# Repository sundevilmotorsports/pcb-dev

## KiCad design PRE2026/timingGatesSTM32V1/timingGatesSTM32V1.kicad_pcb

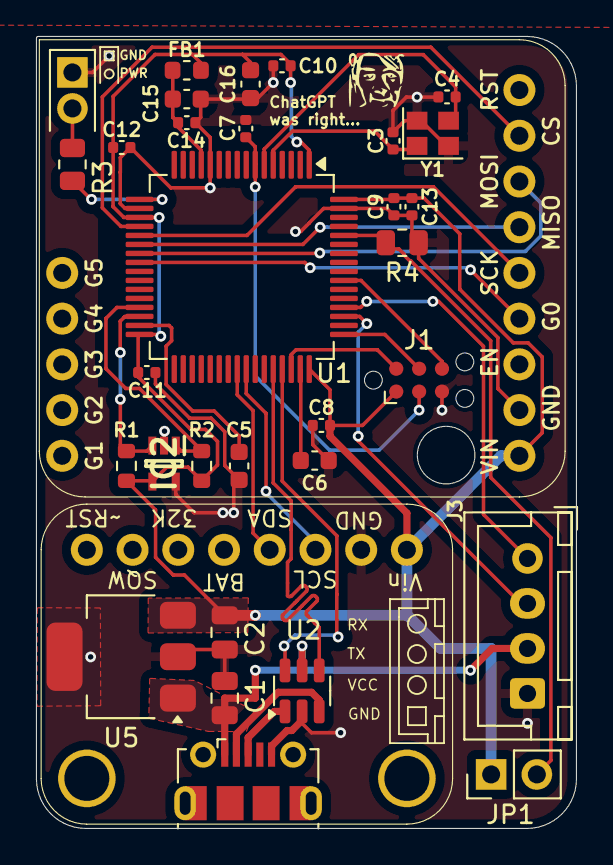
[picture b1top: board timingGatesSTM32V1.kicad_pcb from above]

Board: 4 copper layers, 30.0 x 44.0 mm, 34 parts (0 on the bottom side), 30 nets.

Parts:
C1, C2: 10uF; C_0805_2012Metric
C3, C4: 10pF; C_0402_1005Metric
C5, C6: 2.2uF; C_0603_1608Metric
C7, C8, C9, C10, C11, C12, C13, C14: 100nF; C_0402_1005Metric
C15, C16: 1uF; C_0603_1608Metric
D1: RED (floating); LED_0805_2012Metric
FB1: 120R; L_0603_1608Metric
H1: M3; MountingHole_3.2mm_M3
IC2: 24LC01BT-E_LT; SOT65P210X110-5N
J1: Conn_ARM_SWD_TagConnect_TC2030; Tag-Connect_TC2030-IDC-NL_2x03_P1.27mm_Vertical
J2: USB_B_Micro; USB_Micro-B_Molex-105017-0001
J3: Conn_01x04_Socket; JST_XH_B4B-XH-A_1x04_P2.50mm_Vertical
JP1: BOOT; PinHeader_1x02_P2.54mm_Vertical
R1, R2: 2.7k; R_0603_1608Metric
R3: 220; R_0805_2012Metric
R4: 10k; R_0805_2012Metric
U1: STM32F405RGT6; LQFP-64_10x10mm_P0.5mm
U2: USBLC6-2SC6; SOT-23-6
U3: RFM95W
U4: DS3231
U5: MIC37100-3.3WS; SOT-223-3_TabPin2
Y1: 12MHz; Crystal_SMD_2520-4Pin_2.5x2.0mm

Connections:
+3.3V: C2.1, C8.2, C9.2, C10.2, C11.2, C12.2, C13.2, C16.2, FB1.2, IC2.4 (VCC), J1.1 (VCC), JP1.1 (A), R1.2, R2.2, U1.1 (VBAT), U1.19 (VDD), U1.32 (VDD), U1.48 (VDD), U1.64 (VDD), U3.1 (Vin), U4.1 (Vin), U5.3 (OUT)
/BOOT0: JP1.2 (B), R4.2, U1.60 (BOOT0)
/G0: U1.24 (PC4), U3.4 (G0)
/HSE_IN: C3.1, U1.5 (PH0), Y1.1
/HSE_OUT: C4.1, U1.6 (PH1), Y1.3
/I2C2_SCL: IC2.1 (SCL), R2.1, U1.29 (PB10)
/I2C2_SDA: IC2.3 (SDA), R1.1, U1.30 (PB11)
/I2C3_SCL: U1.41 (PA8), U4.3 (SCL)
/I2C3_SDA: U1.40 (PC9), U4.4 (SDA)
/NRST: C7.2, J1.3 (~RESET), U1.7 (NRST)
/SPI1_MISO: U1.22 (PA6), U3.6 (MISO)
/SPI1_MOSI: U1.23 (PA7), U3.7 (MOSI)
/SPI1_NSS: U1.20 (PA4), U3.8 (CS)
/SPI1_SCK: U1.21 (PA5), U3.5 (SCK)
/SWCLK: J1.4 (SWCLK), U1.49 (PA14)
/SWDIO: J1.2 (SWDIO), U1.46 (PA13)
/SWO: J1.6 (SWO), U1.55 (PB3)
/USART3_RX: J3.1, U1.52 (PC11)
/USART3_TX: J3.2, U1.51 (PC10)
/USB_D+: U1.45 (PA12), U2.6 (I/O1)
/USB_D-: U1.44 (PA11), U2.4 (I/O2)
/VCAP_1: C5.1, U1.31 (VCAP_1)
/VCAP_2: C6.2, U1.47 (VCAP_2)
GND: C1.2, C2.2, C3.2, C4.2, C5.2, C6.1, C7.1, C8.1, C9.1, C10.1, C11.1, C12.1, C13.1, C14.1, C15.1, C16.1, D1.1 (K), IC2.2 (Vss), IC2.5 (WP), J1.5 (GND), J2.5 (GND), J3.4, R4.1, U1.12 (VSSA), U1.18 (VSS), U1.63 (VSS), U2.2 (GND), U3.2 (GND), U4.2 (GND), U5.2 (GND), Y1.2, Y1.4
unnamed: D1.2 (A), R3.1
unnamed: J2.3 (D+), U2.1 (I/O1)
unnamed: J2.2 (D-), U2.3 (I/O2)
unnamed: R3.2, U1.17 (PA3)
unnamed: C14.2, C15.2, FB1.1, U1.13 (VDDA)
VCC: C1.1, J2.1 (VBUS), J3.3, U2.5 (VBUS), U5.1 (IN)

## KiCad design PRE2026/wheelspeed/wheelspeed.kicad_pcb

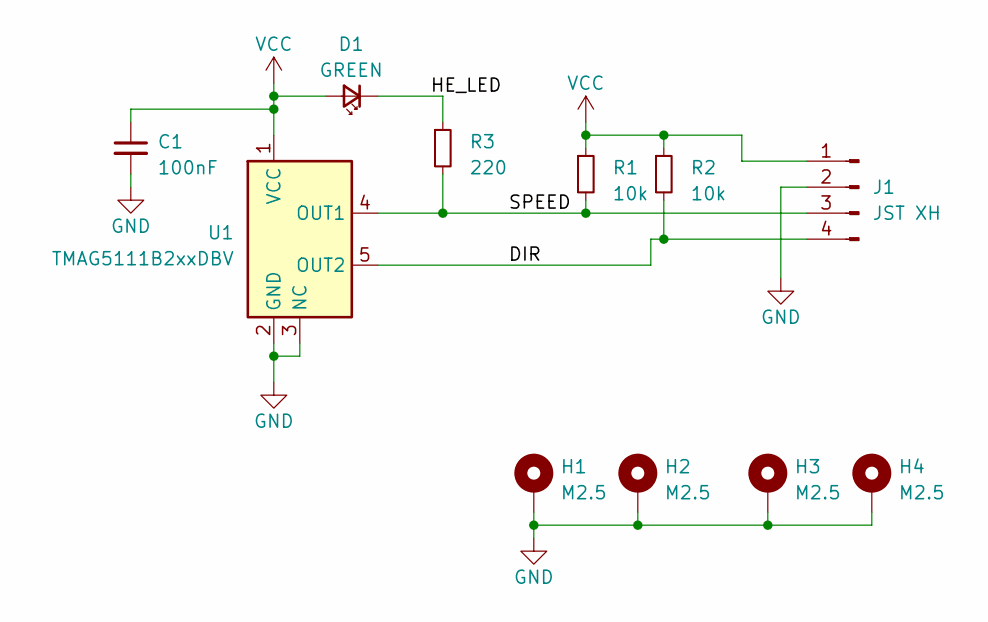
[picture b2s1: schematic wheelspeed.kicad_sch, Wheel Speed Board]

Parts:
C1: 100nF; C_0603_1608Metric
D1: GREEN; LED_1206_3216Metric
H1, H2, H3, H4: M2.5; MountingHole_2.7mm_M2.5_ISO7380_Pad
J1: JST XH; JST_XH_B4B-XH-AM_1x04_P2.50mm_Vertical
R1, R2: 10k; R_0805_2012Metric
R3: 220; R_0805_2012Metric
U1: TMAG5111B2xxDBV; SOT-23-5

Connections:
/DIR: J1.4, R2.2, U1.5 (OUT2)
/HE_LED: D1.1 (K), R3.1
/SPEED: J1.3, R1.2, R3.2, U1.4 (OUT1)
GND: C1.2, H1.1, H2.1, H3.1, H4.1, J1.2, U1.2 (GND), U1.3 (NC)
VCC: C1.1, D1.2 (A), J1.1, R1.1, R2.1, U1.1 (VCC)

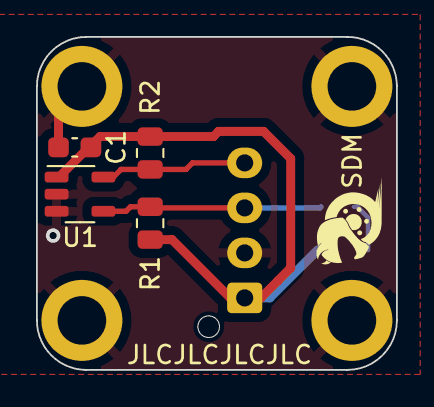
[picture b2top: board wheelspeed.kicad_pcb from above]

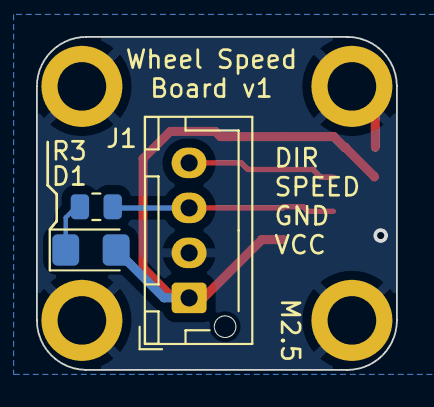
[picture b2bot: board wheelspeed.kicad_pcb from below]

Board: 2 copper layers, 20.0 x 18.5 mm, 11 parts (3 on the bottom side), 5 nets.

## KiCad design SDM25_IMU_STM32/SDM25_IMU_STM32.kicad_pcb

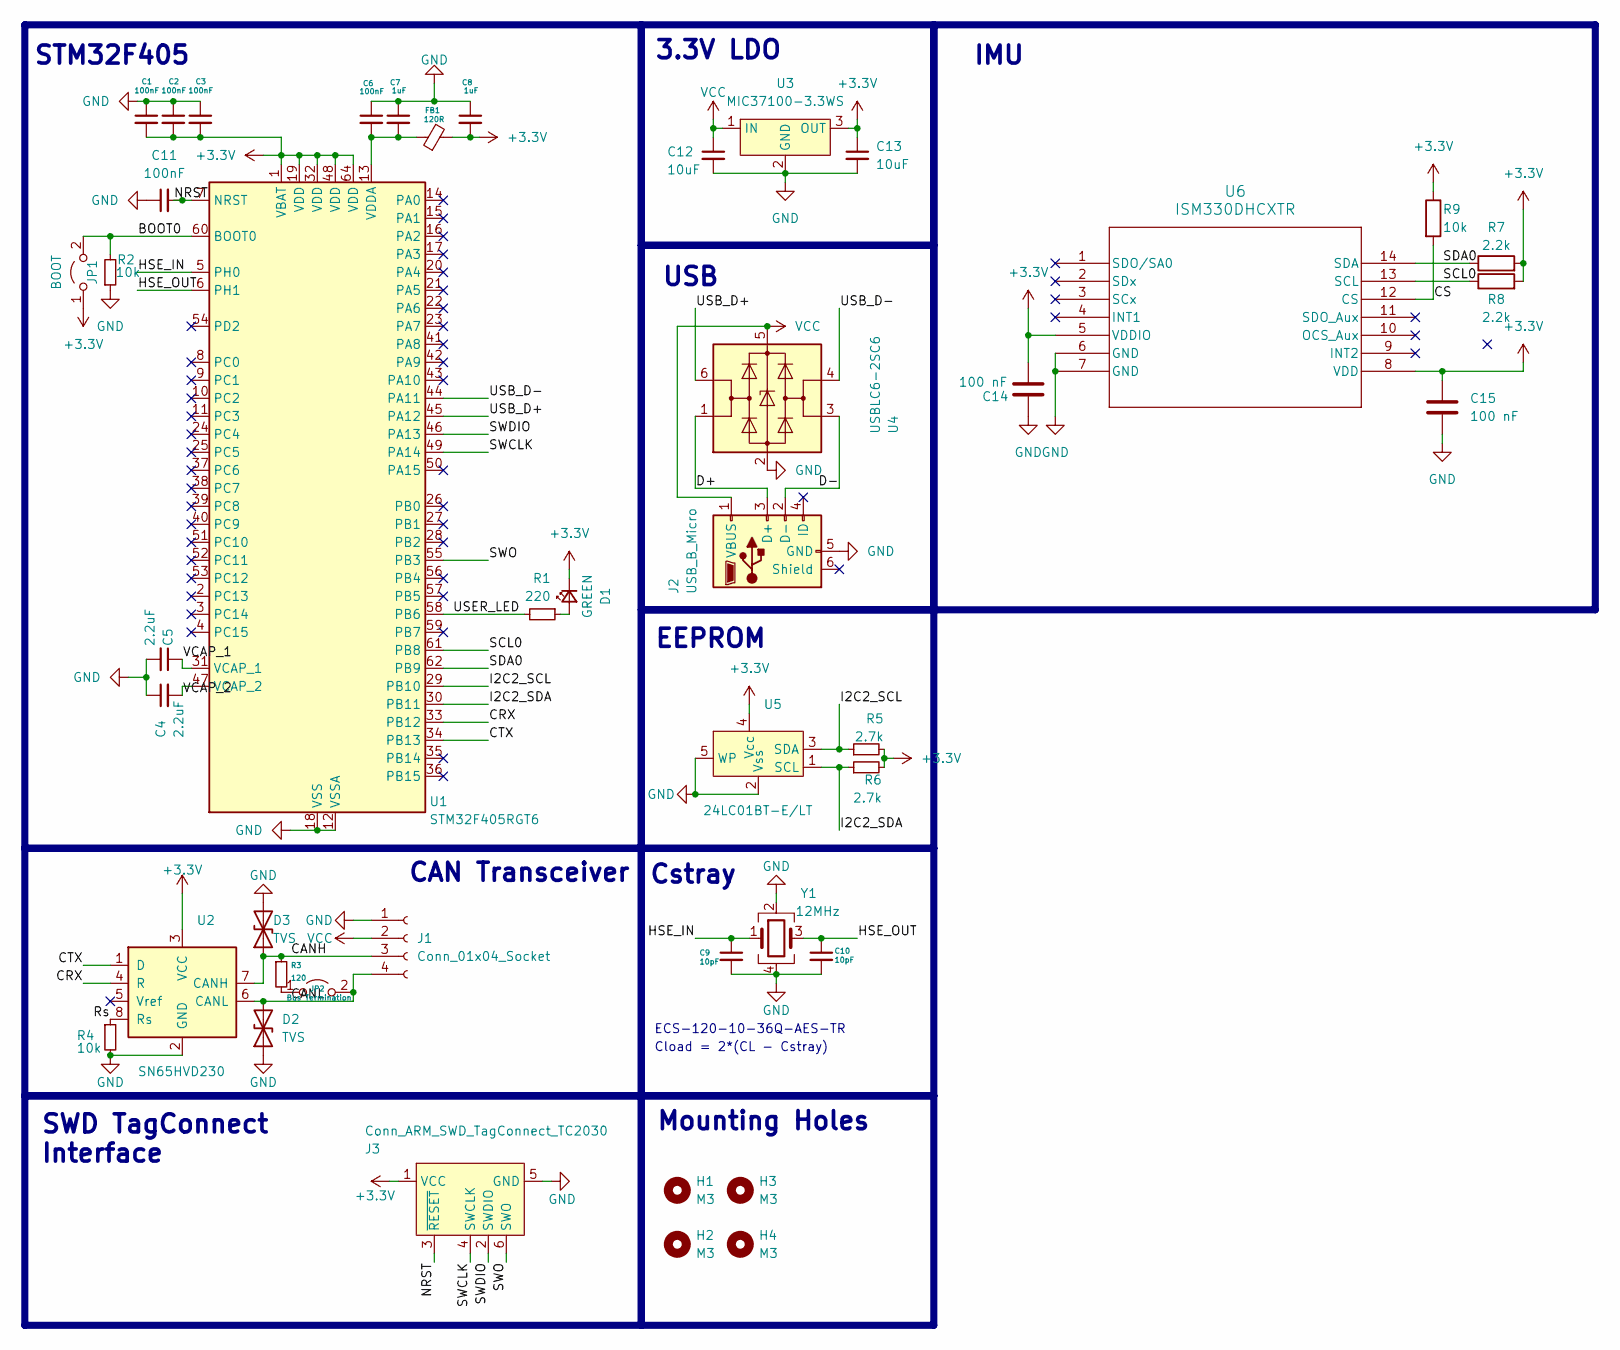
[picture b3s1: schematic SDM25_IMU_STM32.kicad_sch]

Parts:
C1, C2, C3, C6, C11: 100nF; C_0402_1005Metric
C4, C5: 2.2uF; C_0603_1608Metric
C7, C8: 1uF; C_0603_1608Metric
C9, C10: 10pF; C_0402_1005Metric
C12, C13: 10uF; C_0805_2012Metric
C14, C15: 100 nF; C_0402_1005Metric
D1: GREEN; LED_0805_2012Metric
D2, D3: TVS; SOD-123FL
FB1: 120R; L_0603_1608Metric
H1, H2, H3, H4: M3; MountingHole_3.2mm_M3
J1: Conn_01x04_Socket
J2: USB_B_Micro
J3: Conn_ARM_SWD_TagConnect_TC2030; Tag-Connect_TC2030-IDC-NL_2x03_P1.27mm_Vertical
JP1: BOOT; PinHeader_1x02_P2.54mm_Vertical
JP2: Bus Termination; PinHeader_1x02_P2.54mm_Vertical
R1: 220; R_0805_2012Metric
R2, R4, R9: 10k; R_0805_2012Metric
R3: 120; R_0603_1608Metric
R5, R6: 2.7k; R_0603_1608Metric
R7, R8: 2.2k; R_0603_1608Metric
U1: STM32F405RGT6; SOIC-8_3.9x4.9mm_P1.27mm
U2: SN65HVD230; LQFP-64_10x10mm_P0.5mm
U3: MIC37100-3.3WS; SC-70-5
U4: USBLC6-2SC6; SOT-23-6
U5: 24LC01BT-E/LT; SOT-223-3_TabPin2
U6: ISM330DHCXTR; LGA-14L
Y1: 12MHz; Crystal_SMD_2520-4Pin_2.5x2.0mm

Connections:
+3.3V: C1.2, C2.2, C3.2, C8.2, C13.1, C14.2, C15.1, D1.1 (K), FB1.2, J3.1 (VCC), JP1.1 (A), R5.2, R6.2, R7.2, R8.2, R9.1, U1.1 (VBAT), U1.19 (VDD), U1.32 (VDD), U1.48 (VDD), U1.64 (VDD), U2.3 (VCC), U3.3 (OUT), U5.4 (Vcc), U6.5 (VDDIO), U6.8 (VDD)
/BOOT0: JP1.2 (B), R2.2, U1.60 (BOOT0)
/CANH: D3.1 (A1), J1.3, R3.1, U2.7 (CANH)
/CANL: D2.2 (A2), J1.4, JP2.2 (B), U2.6 (CANL)
/CRX: U1.33 (PB13), U2.4 (R)
/CS: R9.2, U6.12 (CS)
/CTX: U1.34 (PB13), U2.1 (D)
/D+: J2.3 (D+), U4.1 (I/O1)
/D-: J2.2 (D-), U4.3 (I/O2)
/HSE_IN: C9.1, U1.5 (PH0), Y1.1
/HSE_OUT: C10.1, U1.6 (PH1), Y1.3
/I2C2_SCL: R5.1, U1.29 (PB10), U5.3 (SDA)
/I2C2_SDA: R6.1, U1.30 (PB11), U5.1 (SCL)
/NRST: C11.2, J3.3 (~RESET), U1.7 (NRST)
/Rs: R4.1, U2.8 (Rs)
/SCL0: R8.1, U1.61 (PB8), U6.13 (SCL)
/SDA0: R7.1, U1.62 (PB9), U6.14 (SDA)
/SWCLK: J3.4 (SWCLK), U1.49 (PA14)
/SWDIO: J3.2 (SWDIO), U1.46 (PA13)
/SWO: J3.6 (SWO), U1.55 (PB3)
/USB_D+: U1.45 (PA12), U4.6 (I/O1)
/USB_D-: U1.44 (PA11), U4.4 (I/O2)
/USER_LED: R1.2, U1.58 (PB6)
/VCAP_1: C5.1, U1.31 (VCAP_1)
/VCAP_2: C4.2, U1.47 (VCAP_2)
GND: C1.1, C2.1, C3.1, C4.1, C5.2, C6.1, C7.1, C8.1, C9.2, C10.2, C11.1, C12.2, C13.2, C14.1, C15.2, D2.1 (A1), D3.2 (A2), J1.1, J2.5 (GND), J3.5 (GND), R2.1, R4.2, U1.12 (VSSA), U1.18 (VSS), U1.63 (VSS), U2.2 (GND), U3.2 (GND), U4.2 (GND), U5.2 (Vss), U5.5 (WP), U6.6 (GND), U6.7 (GND), Y1.2, Y1.4
unnamed: D1.2 (A), R1.1
unnamed: JP2.1 (A), R3.2
unnamed: C6.2, C7.2, FB1.1, U1.13 (VDDA)
VCC: C12.1, J1.2, J2.1 (VBUS), U3.1 (IN), U4.5 (VBUS)

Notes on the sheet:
EEPROM
STM32F405
Cload = 2*(CL - Cstray)
IMU
Cstray
SWD TagConnect Interface
CAN Transceiver
ECS-120-10-36Q-AES-TR
3.3V LDO
USB
Mounting Holes

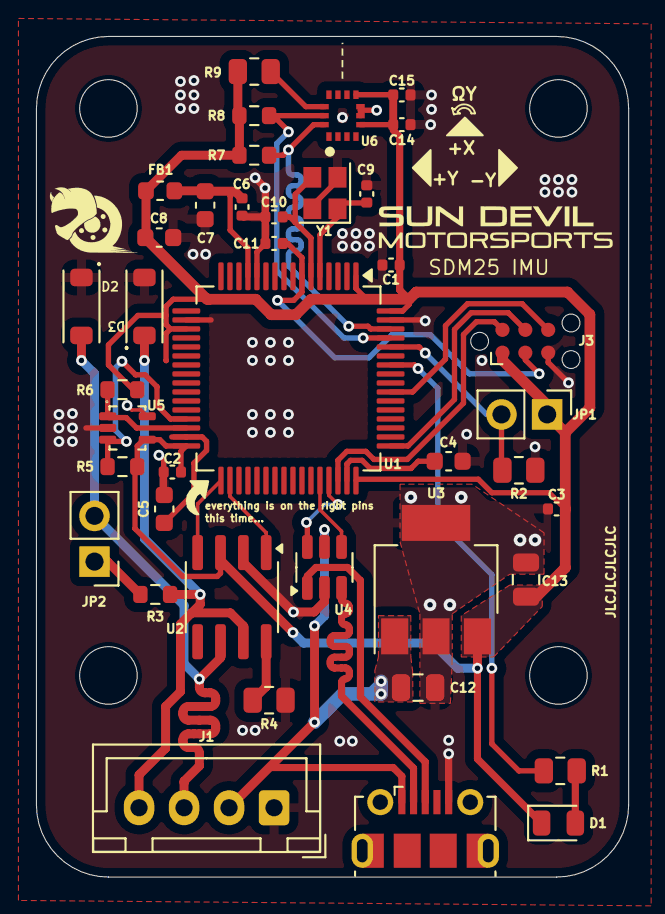
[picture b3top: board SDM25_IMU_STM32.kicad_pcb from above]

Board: 4 copper layers, 32.9 x 46.7 mm, 44 parts (0 on the bottom side), 30 nets.

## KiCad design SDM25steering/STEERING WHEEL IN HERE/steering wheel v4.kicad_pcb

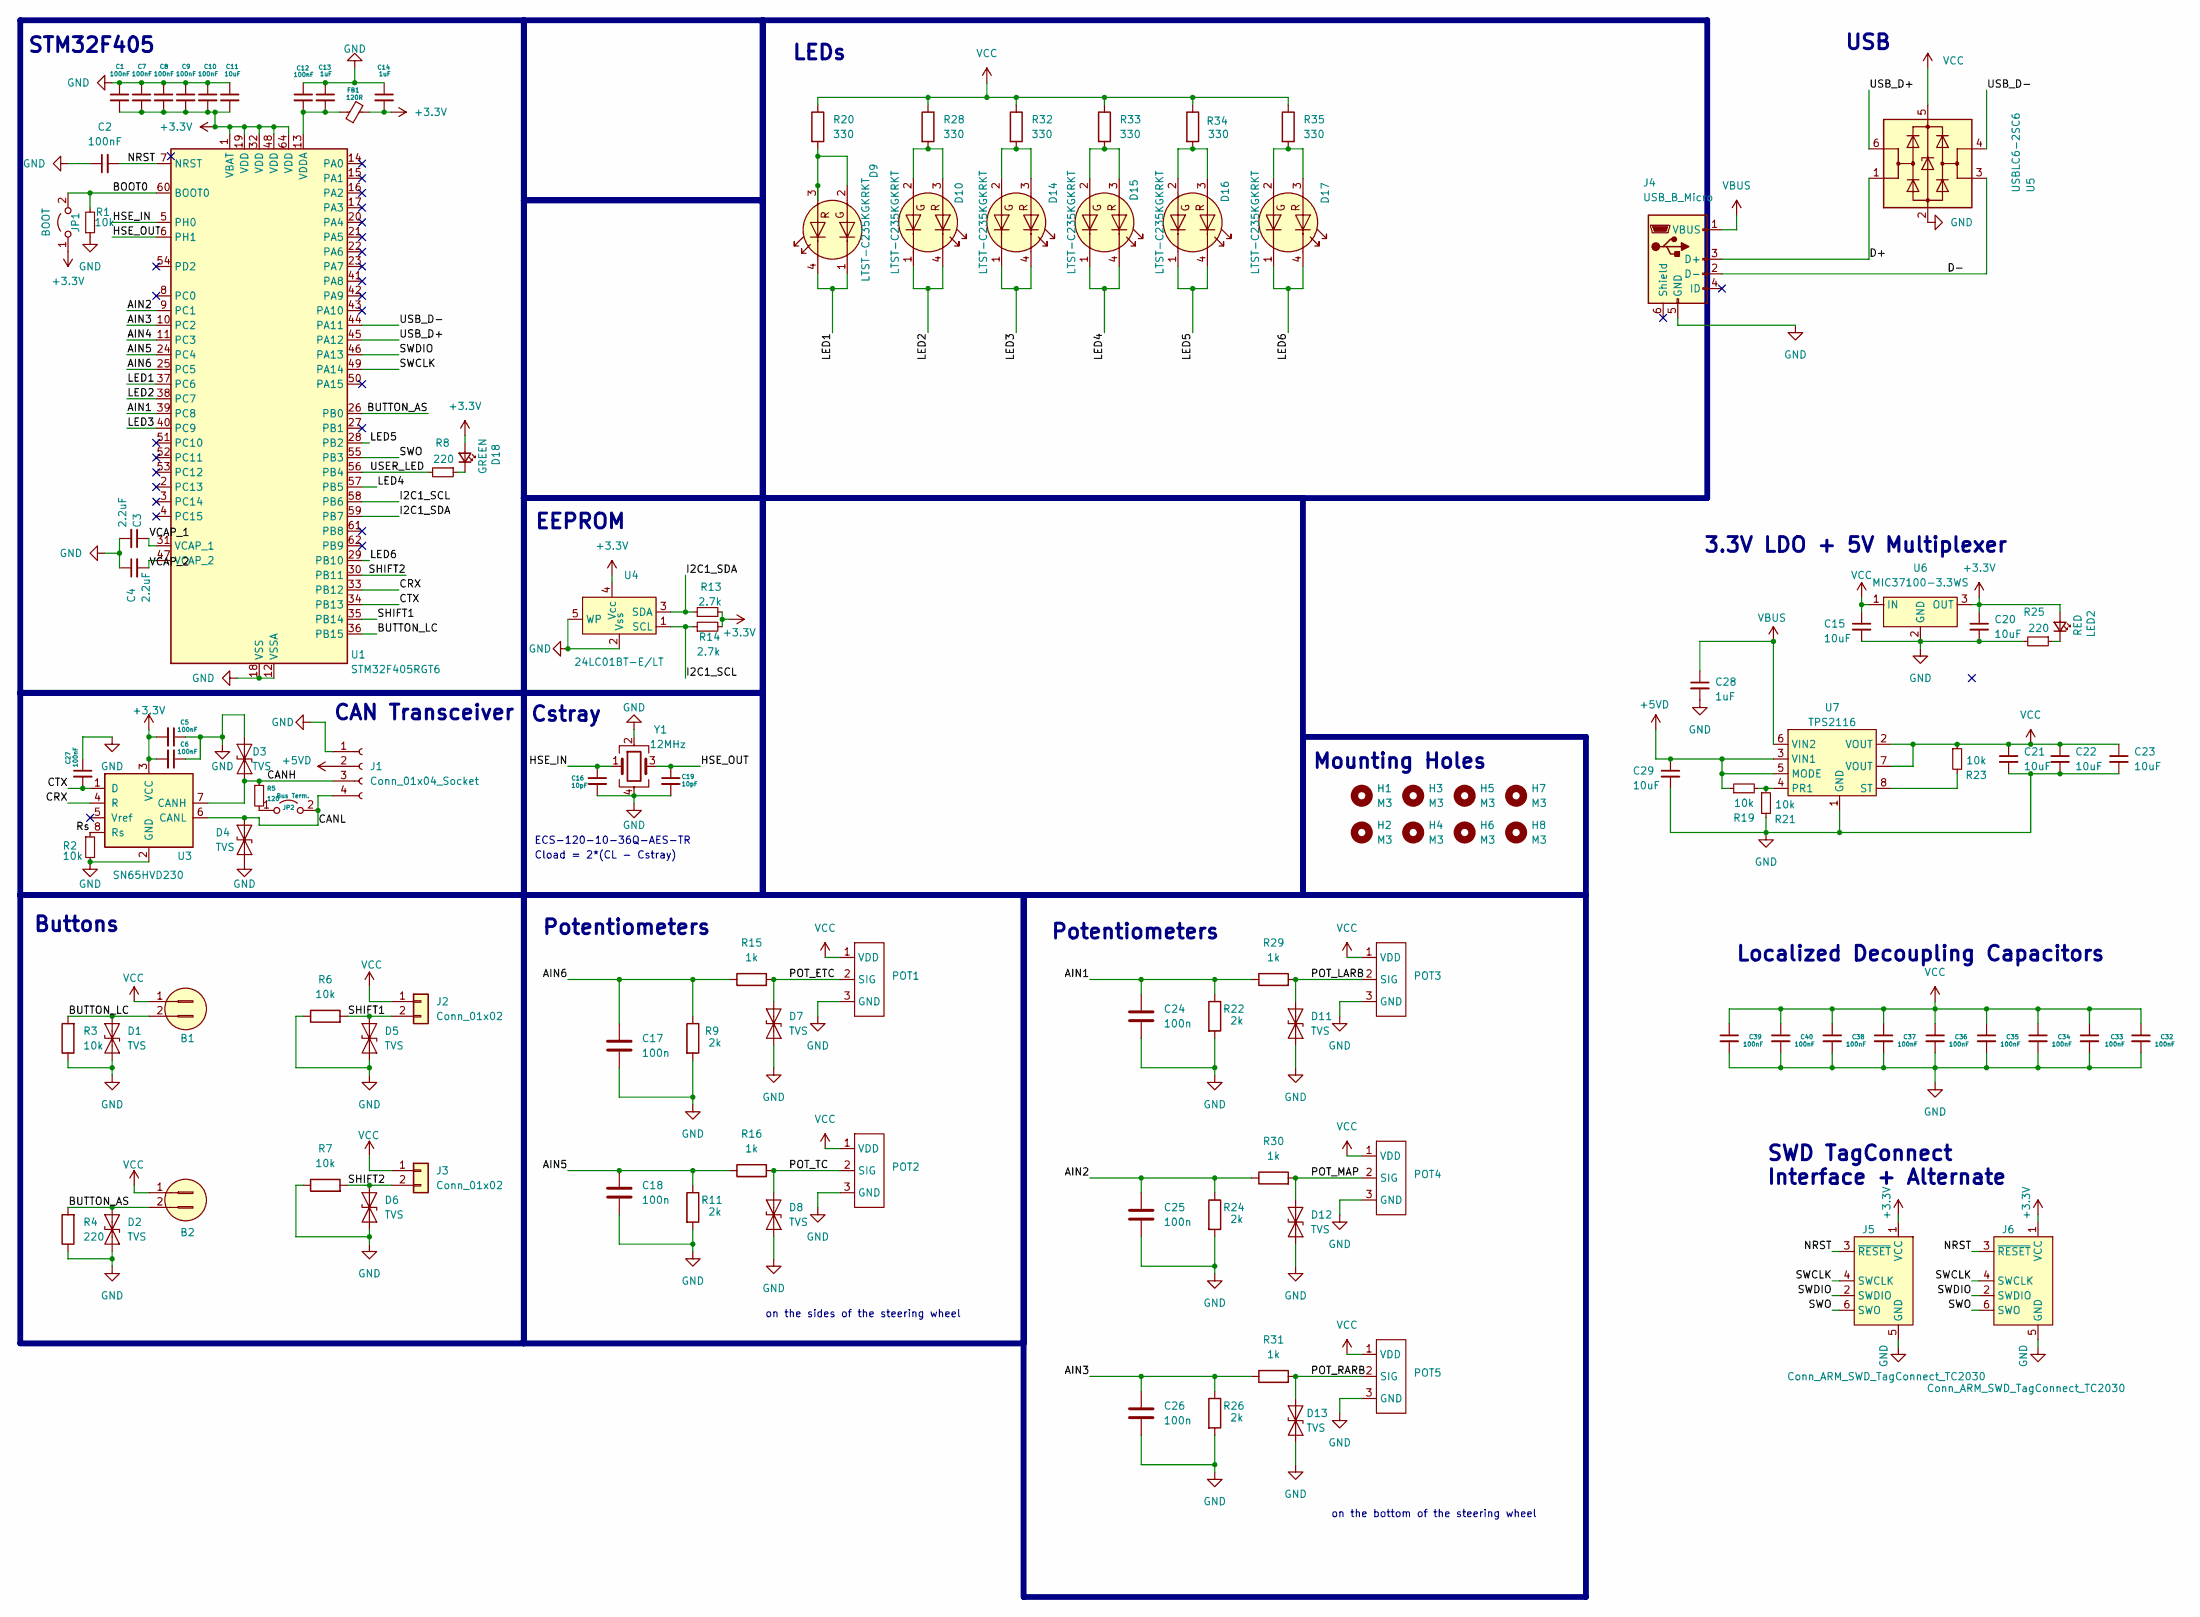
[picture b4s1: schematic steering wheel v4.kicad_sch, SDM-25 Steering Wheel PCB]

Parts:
B1, B2: Conn_01x02; 8631CQD2
C1, C2, C5, C6, C7, C8, C9, C10, C12, C27, C32, C33, C34, C35, C36, C37, C38, C39, C40: 100nF; C_0402_1005Metric
C3, C4: 2.2uF; C_0603_1608Metric
C11, C15, C20, C21, C22, C23, C29: 10uF; C_0805_2012Metric
C13, C14, C28: 1uF; C_0603_1608Metric
C16, C19: 10pF; C_0402_1005Metric
C17, C18, C24, C25, C26: 100n; C_0402_1005Metric
D1, D2, D5, D6, D7, D8, D11, D12, D13: TVS; D_SOD-323_HandSoldering
D3, D4: TVS; SOD-123FL
D9, D10, D14, D15, D16, D17: LTST-C235KGKRKT; LED_Cree-PLCC4_5x5mm_CW
D18: GREEN; LED_0805_2012Metric
FB1: 120R; L_0603_1608Metric
H1, H2, H3, H4, H5, H6, H7, H8: M3; MountingHole_3.2mm_M3
J1: Conn_01x04_Socket; JST_EH_S4B-EH_1x04_P2.50mm_Horizontal
J2, J3: Conn_01x02; JST_EH_S2B-EH_1x02_P2.50mm_Horizontal
J4: USB_B_Micro; USB_Micro-B_Molex-105017-0001
J5, J6: Conn_ARM_SWD_TagConnect_TC2030; Tag-Connect_TC2030-IDC-NL_2x03_P1.27mm_Vertical
JP1: BOOT; PinHeader_1x02_P2.54mm_Vertical
JP2: Bus Term.; PinHeader_1x02_P2.54mm_Vertical
LED2: RED; LED_0805_2012Metric
POT1, POT2, POT3: PEC11R-4315F-S0012
POT4, POT5: P081N-271F2CBR10K
R1, R2: 10k; R_0805_2012Metric
R3, R6, R7, R19, R21, R23: 10k; R_0603_1608Metric
R4, R8, R25: 220; R_0603_1608Metric
R5: 120; R_0603_1608Metric
R9, R11, R22, R24, R26: 2k; R_0603_1608Metric
R13, R14: 2.7k; R_0603_1608Metric
R15, R16, R29, R30, R31: 1k; R_0603_1608Metric
R20, R28, R32, R33, R34, R35: 330; R_0603_1608Metric
U1: STM32F405RGT6; LQFP-64_10x10mm_P0.5mm
U3: SN65HVD230; SOIC-8_3.9x4.9mm_P1.27mm
U4: 24LC01BT-E/LT; SOT-353_SC-70-5
U5: USBLC6-2SC6; SOT-23-6
U6: MIC37100-3.3WS; SOT-223-3_TabPin2
U7: TPS2116; SOT-5X3
Y1: 12MHz; Crystal_SMD_2520-4Pin_2.5x2.0mm

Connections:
+3.3V: C1.2, C5.2, C6.2, C7.2, C8.2, C9.2, C10.2, C11.2, C14.2, C20.1, D18.2 (A), FB1.2, J5.1 (VCC), J6.1 (VCC), JP1.1 (A), LED2.2 (A), R13.2, R14.2, U1.1 (VBAT), U1.19 (VDD), U1.32 (VDD), U1.48 (VDD), U1.64 (VDD), U3.3 (VCC), U4.4 (Vcc), U6.3 (OUT)
+5VD: C29.1, J1.2, R19.1, U7.3 (VIN1), U7.5 (MODE)
/AIN1: C24.1, R22.1, R29.1, U1.39 (PC8)
/AIN2: C25.1, R24.1, R30.1, U1.9 (PC1)
/AIN3: C26.1, R26.1, R31.1, U1.10 (PC2)
/AIN4: U1.11 (PC3)
/AIN5: C18.1, R11.1, R16.1, U1.24 (PC4)
/AIN6: C17.1, R9.1, R15.1, U1.25 (PC5)
/BOOT0: JP1.2 (B), R1.2, U1.60 (BOOT0)
/BUTTON_AS: B2.2, D2.2 (A2), R4.2, U1.26 (PB0)
/BUTTON_LC: B1.2, D1.2 (A2), R3.2, U1.36 (PB15)
/CANH: D3.1 (A1), J1.3, R5.1, U3.7 (CANH)
/CANL: D4.2 (A2), J1.4, JP2.2 (B), U3.6 (CANL)
/CRX: U1.33 (PB12), U3.4 (R)
/CTX: C27.2, U1.34 (PB13), U3.1 (D)
/D+: J4.3 (D+), U5.1 (I/O1)
/D-: J4.2 (D-), U5.3 (I/O2)
/HSE_IN: C16.1, U1.5 (PH0), Y1.1
/HSE_OUT: C19.1, U1.6 (PH1), Y1.3
/I2C1_SCL: R14.1, U1.58 (PB6), U4.1 (SCL)
/I2C1_SDA: R13.1, U1.59 (PB7), U4.3 (SDA)
/LED1: D9.1 (K2), D9.4 (K1), U1.37 (PC6)
/LED2: D10.1 (K2), D10.4 (K1), U1.38 (PC7)
/LED3: D14.1 (K2), D14.4 (K1), U1.40 (PC9)
/LED4: D15.1 (K2), D15.4 (K1), U1.57 (PB5)
/LED5: D16.1 (K2), D16.4 (K1), U1.28 (PB2)
/LED6: D17.1 (K2), D17.4 (K1), U1.29 (PB10)
/NRST: C2.2, J5.3 (~RESET), J6.3 (~RESET), U1.7 (NRST)
/POT_ETC: D7.2 (A2), POT1.2 (VDD), R15.2
/POT_LARB: D11.2 (A2), POT3.2 (SIG), R29.2
/POT_MAP: D12.2 (A2), POT4.2 (SIG), R30.2
/POT_RARB: D13.2 (A2), POT5.2 (SIG), R31.2
/POT_TC: D8.2 (A2), POT2.2 (SIG), R16.2
/Rs: R2.1, U3.8 (Rs)
/SHIFT1: D5.2 (A2), J2.2, R6.2, U1.35 (PB14)
/SHIFT2: D6.2 (A2), J3.2, R7.2, U1.30 (PB11)
/SWCLK: J5.4 (SWCLK), J6.4 (SWCLK), U1.49 (PA14)
/SWDIO: J5.2 (SWDIO), J6.2 (SWDIO), U1.46 (PA13)
/SWO: J5.6 (SWO), J6.6 (SWO), U1.55 (PB3)
/USB_D+: U1.45 (PA12), U5.6 (I/O1)
/USB_D-: U1.44 (PA11), U5.4 (I/O2)
/USER_LED: R8.2, U1.56 (PB4)
/VCAP_1: C3.1, U1.31 (VCAP_1)
/VCAP_2: C4.2, U1.47 (VCAP_2)
GND: C1.1, C2.1, C3.2, C4.1, C5.1, C6.1, C7.1, C8.1, C9.1, C10.1, C11.1, C12.1, C13.1, C14.1, C15.2, C16.2, C17.2, C18.2, C19.2, C20.2, C21.2, C22.2, C23.2, C24.2, C25.2, C26.2, C27.1, C28.2, C29.2, C32.2, C33.2, C34.2, C35.2, C36.2, C37.2, C38.2, C39.2, C40.2, D1.1 (A1), D2.1 (A1), D3.2 (A2), D4.1 (A1), D5.1 (A1), D6.1 (A1), D7.1 (A1), D8.1 (A1), D11.1 (A1), D12.1 (A1), D13.1 (A1), J1.1, J4.5 (GND), J5.5 (GND), J6.5 (GND), POT1.3 (VDD), POT2.3 (GND), POT3.3 (GND), POT4.3 (GND), POT5.3 (GND), R1.1, R2.2, R3.1, R4.1, R6.1, R7.1, R9.2, R11.2, R21.2, R22.2, R24.2, R25.2, R26.2, U1.12 (VSSA), U1.18 (VSS), U1.63 (VSS), U3.2 (GND), U4.2 (Vss), U4.5 (WP), U5.2 (GND), U6.2 (GND), U7.1 (GND), Y1.2, Y1.4
unnamed: D9.2 (A2), D9.3 (A1), R20.2
unnamed: D10.2 (A2), D10.3 (A1), R28.2
unnamed: D14.2 (A2), D14.3 (A1), R32.2
unnamed: D15.2 (A2), D15.3 (A1), R33.2
unnamed: D16.2 (A2), D16.3 (A1), R34.2
unnamed: D17.2 (A2), D17.3 (A1), R35.2
unnamed: D18.1 (K), R8.1
unnamed: JP2.1 (A), R5.2
unnamed: LED2.1 (K), R25.1
unnamed: C12.2, C13.2, FB1.1, U1.13 (VDDA)
unnamed: R19.2, R21.1, U7.4 (PR1)
unnamed: R23.2, U7.8 (ST)
VBUS: C28.1, J4.1 (VBUS), U7.6 (VIN2)
VCC: B1.1, B2.1, C15.1, C21.1, C22.1, C23.1, C32.1, C33.1, C34.1, C35.1, C36.1, C37.1, C38.1, C39.1, C40.1, J2.1, J3.1, POT1.1 (VDD), POT2.1 (VDD), POT3.1 (VDD), POT4.1 (VDD), POT5.1 (VDD), R20.1, R23.1, R28.1, R32.1, R33.1, R34.1, R35.1, U5.5 (VBUS), U6.1 (IN), U7.2 (VOUT), U7.7 (VOUT)

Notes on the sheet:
Cstray
CAN Transceiver
Localized Decoupling Capacitors
Buttons
STM32F405
on the bottom of the steering wheel
Mounting Holes
Potentiometers
SWD TagConnect Interface + Alternate
USB
LEDs
on the sides of the steering wheel
3.3V LDO + 5V Multiplexer
Cload = 2*(CL - Cstray)
EEPROM
ECS-120-10-36Q-AES-TR

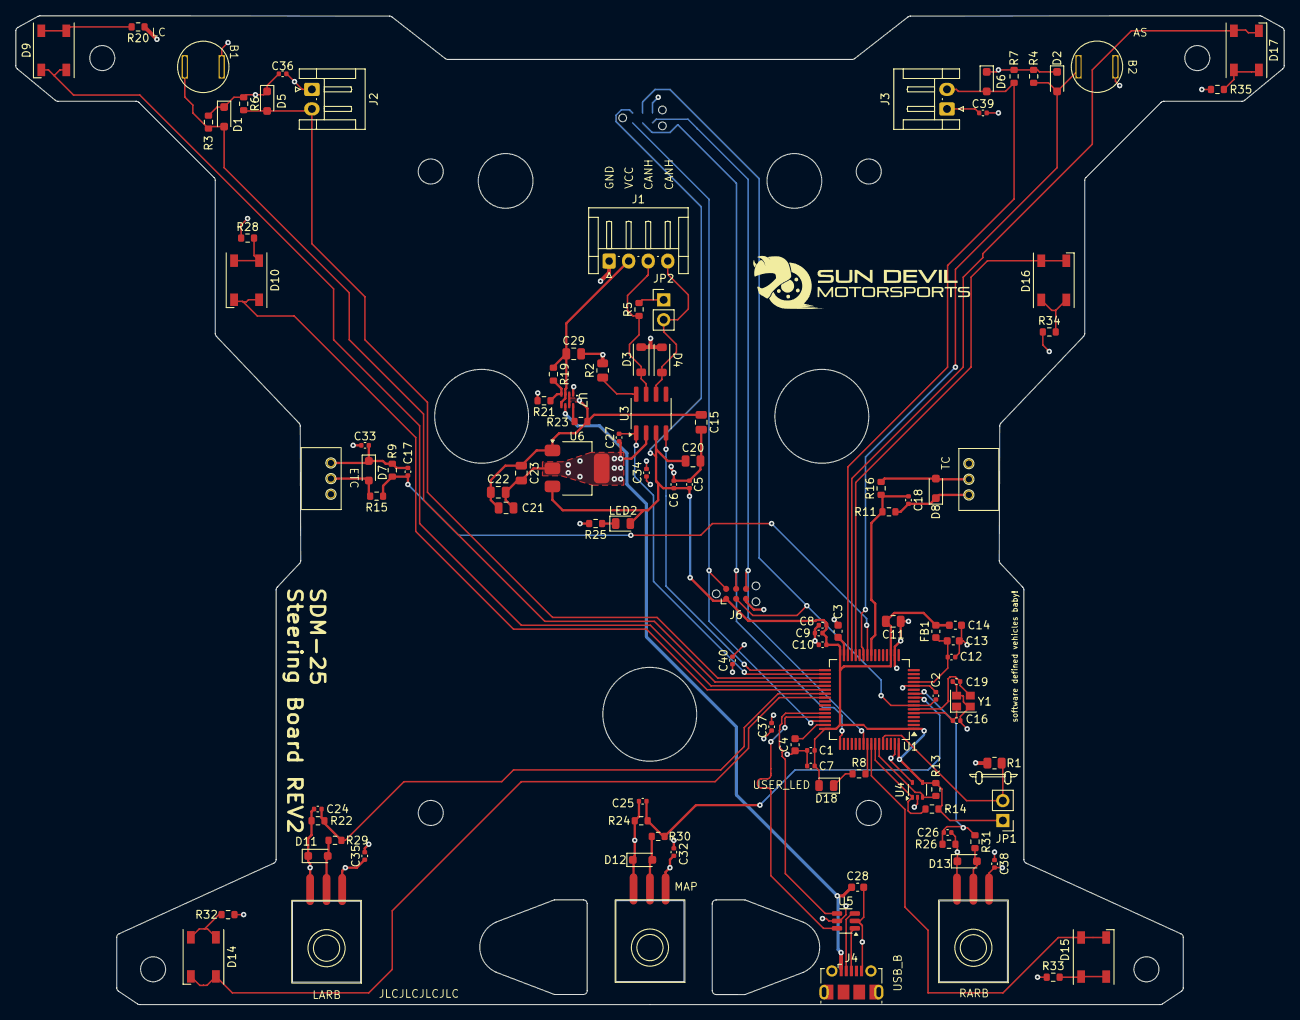
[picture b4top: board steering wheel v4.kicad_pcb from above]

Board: 4 copper layers, 162.2 x 126.4 mm, 118 parts (1 on the bottom side), 58 nets.

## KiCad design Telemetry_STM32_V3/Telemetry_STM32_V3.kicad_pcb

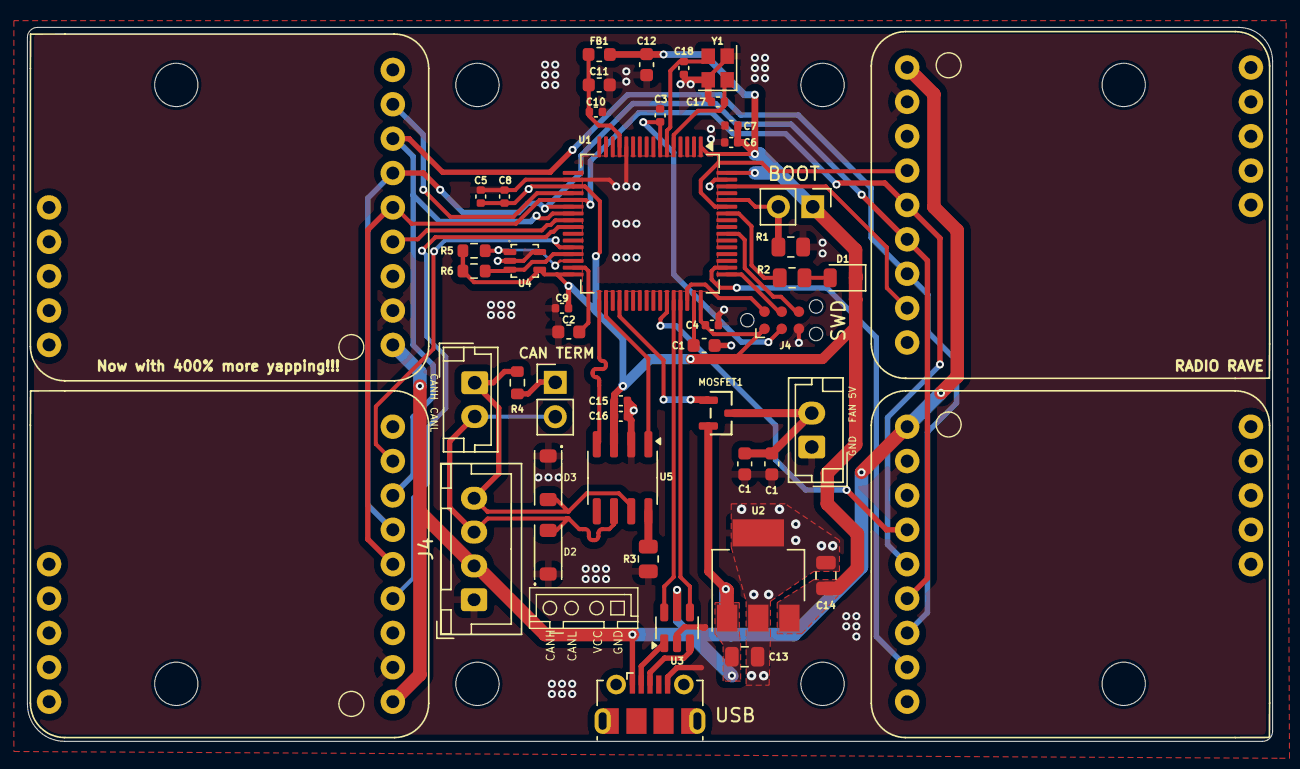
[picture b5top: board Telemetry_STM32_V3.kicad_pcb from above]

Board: 4 copper layers, 92.0 x 52.8 mm, 53 parts (0 on the bottom side), 39 nets.

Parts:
C1, C1#2: 100nF; C_0603_1608Metric
C1#3, C2: 2.2uF; C_0603_1608Metric
C3, C4, C5, C6, C7, C8, C9, C10, C15, C16: 100nF; C_0402_1005Metric
C11, C12: 1uF; C_0603_1608Metric
C13, C14: 10uF; C_0805_2012Metric
C17, C18: 10pF; C_0402_1005Metric
D1: GREEN; LED_0805_2012Metric
D2, D3: TVS; SOD-123FL
FB1: 120R; L_0603_1608Metric
H1, H1#2, H1#3, H1#4, H1#5, H2, H3, H4: M3; MountingHole_3.2mm_M3
J4: USB_B_Micro; USB_Micro-B_Molex-105017-0001
J4#2: Conn_ARM_SWD_TagConnect_TC2030; Tag-Connect_TC2030-IDC-NL_2x03_P1.27mm_Vertical
J4#3: JST-XH; JST_XH_B4B-XH-A_1x04_P2.50mm_Vertical
JP1: BOOT; PinHeader_1x02_P2.54mm_Vertical
JP2: Bus Termination; PinHeader_1x02_P2.54mm_Vertical
R1, R3: 10k; R_0805_2012Metric
R2: 220; R_0805_2012Metric
R4: 120; R_0603_1608Metric
R5, R6: 2.7k; R_0603_1608Metric
U1: STM32F405RGT6; LQFP-64_10x10mm_P0.5mm
U2: MIC37100-3.3WS; SOT-223-3_TabPin2
U3, U3#3, U3#4, U3#5: RFM95W
U3#2: USBLC6-2SC6; SOT-23-6
U4: 24LC01BT-E/LT; SC-70-5
U5: SN65HVD230; SOIC-8_3.9x4.9mm_P1.27mm
Y1: 12MHz; Crystal_SMD_2520-4Pin_2.5x2.0mm

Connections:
+3.3V: C4.2, C5.2, C6.2, C7.2, C8.2, C9.2, C12.2, C14.1, C15.2, C16.2, D1.1 (K), FB1.2, J4#2.1 (VCC), JP1.1 (A), R5.2, R6.2, U1.1 (VBAT), U1.19 (VDD), U1.32 (VDD), U1.48 (VDD), U1.64 (VDD), U2.3 (OUT), U4.4 (Vcc), U5.3 (VCC)
/BOOT0: JP1.2 (B), R1.2, U1.60 (BOOT0)
/CRX: U1.33 (PB12), U5.4 (R)
/CS_1: U1.20 (PA4), U3.8 (CS)
/CS_2: U1.28 (PB2), U3#5.8 (CS)
/CS_3: U1.62 (PB9), U3#4.8 (CS)
/CS_4: U1.50 (PA15), U3#3.8 (CS)
/CTX: U1.34 (PB13), U5.1 (D)
/G0_1: U1.24 (PC4), U3.4 (G0)
/G0_2: U1.25 (PC5), U3#5.4 (G0)
/G0_3: U1.59 (PB7), U3#4.4 (G0)
/G0_4: U1.43 (PA10), U3#3.4 (G0)
/HSE_IN: C17.1, U1.5 (PH0), Y1.1
/HSE_OUT: C18.1, U1.6 (PH1), Y1.3
/I2C2_SCL: R6.1, U1.29 (PB10), U4.3 (SDA)
/I2C2_SDA: R5.1, U1.30 (PB11), U4.1 (SCL)
/MISO: U1.22 (PA6), U3.6 (MISO), U3#3.6 (MISO), U3#4.6 (MISO), U3#5.6 (MISO)
/MOSI: U1.23 (PA7), U3.7 (MOSI), U3#3.7 (MOSI), U3#4.7 (MOSI), U3#5.7 (MOSI)
/NRST: C3.2, J4#2.3 (~RESET), U1.7 (NRST)
/SCK: U1.21 (PA5), U3.5 (SCK), U3#3.5 (SCK), U3#4.5 (SCK), U3#5.5 (SCK)
/SWCLK: J4#2.4 (SWCLK), U1.49 (PA14)
/SWDIO: J4#2.2 (SWDIO), U1.46 (PA13)
/SWO: J4#2.6 (SWO), U1.55 (PB3)
/USB_D+: U1.45 (PA12), U3#2.4 (I/O2)
/USB_D-: U1.44 (PA11), U3#2.6 (I/O1)
/USER_LED: R2.2, U1.58 (PB6)
CANH: D3.2 (A2), J4#3.4, R4.1, U5.7 (CANH)
CANL: D2.2 (A2), J4#3.3, JP2.2 (B), U5.6 (CANL)
FAN_PWR: C1.1, C1#2.1
GND: C1.2, C1#2.2, C1#3.1, C2.2, C3.1, C4.1, C5.1, C6.1, C7.1, C8.1, C9.1, C10.1, C11.1, C12.1, C13.2, C14.2, C15.1, C16.1, C17.2, C18.2, D2.1 (A1), D3.1 (A1), J4.5 (GND), J4#2.5 (GND), J4#3.1, R1.1, R3.2, U1.12 (VSSA), U1.18 (VSS), U1.63 (VSS), U2.2 (GND), U3.2 (GND), U3#2.2 (GND), U3#3.2 (GND), U3#4.2 (GND), U3#5.2 (GND), U4.2 (Vss), U4.5 (WP), U5.2 (GND), Y1.2, Y1.4
unnamed: D1.2 (A), R2.1
unnamed: J4.3 (D+), U3#2.3 (I/O2)
unnamed: J4.2 (D-), U3#2.1 (I/O1)
unnamed: JP2.1 (A), R4.2
unnamed: C2.1, U1.31 (VCAP_1)
unnamed: C1#3.2, U1.47 (VCAP_2)
unnamed: C10.2, C11.2, FB1.1, U1.13 (VDDA)
unnamed: R3.1, U5.8 (Rs)
VCC: C13.1, J4.1 (VBUS), J4#3.2, U2.1 (IN), U3.1 (Vin), U3#2.5 (VBUS), U3#3.1 (Vin), U3#4.1 (Vin), U3#5.1 (Vin)

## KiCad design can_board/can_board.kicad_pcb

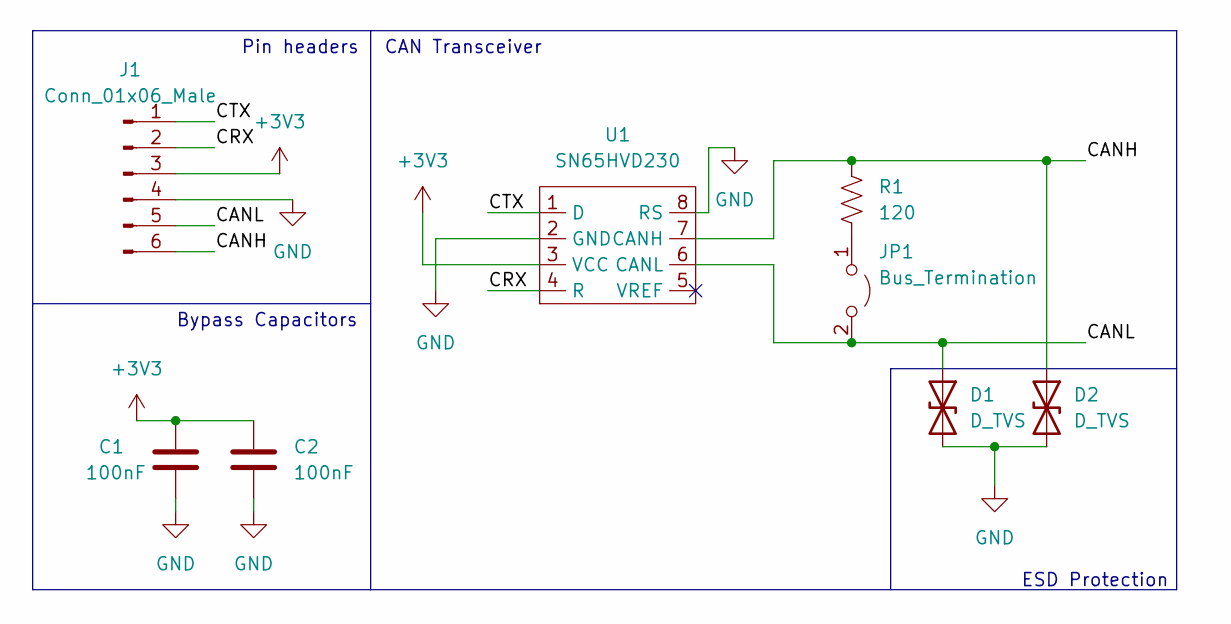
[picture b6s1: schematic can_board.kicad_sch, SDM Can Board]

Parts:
C1, C2: 100nF; CP_EIA-1608-08_AVX-J
D1, D2: D_TVS; D_0805_2012Metric
J1: Conn_01x06_Male; PinHeader_1x06_P2.54mm_Vertical
JP1: Bus_Termination; PinHeader_1x02_P2.54mm_Vertical
R1: 120; R_0805_2012Metric
U1: SN65HVD230; SOIC-8_3.9x4.9mm_P1.27mm

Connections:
+3V3: C1.1, C2.1, J1.3, U1.3 (VCC)
/CANH: D2.1 (A1), J1.6, R1.1, U1.7 (CANH)
/CANL: D1.1 (A1), J1.5, JP1.2 (B), U1.6 (CANL)
/CRX: J1.2, U1.4 (R)
/CTX: J1.1, U1.1 (D)
GND: C1.2, C2.2, D1.2 (A2), D2.2 (A2), J1.4, U1.2 (GND), U1.8 (RS)
unnamed: JP1.1 (A), R1.2

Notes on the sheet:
Bypass Capacitors
Pin headers
ESD Protection
CAN Transceiver

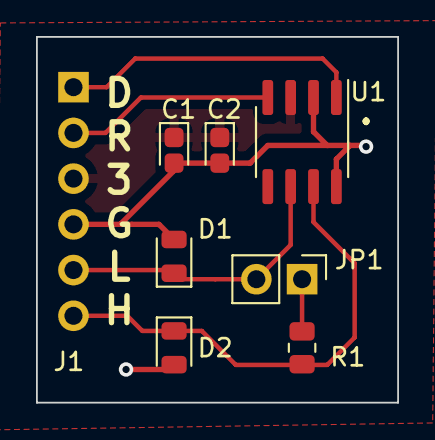
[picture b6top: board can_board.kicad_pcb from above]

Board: 2 copper layers, 20.1 x 20.3 mm, 8 parts (1 on the bottom side), 7 nets.
